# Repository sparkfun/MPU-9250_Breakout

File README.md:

9 Degrees of Freedom - MPU-9250 Breakout
========================================

[*9 Degrees of Freedom - MPU-9250 Breakout (SEN-13762)*](https://www.sparkfun.com/products/13762)

The MPU-9250 is an accelerometer, gyro, and magnetometer all in a single package with an I<sup>2</sup>C. [The datasheet can be found here.](https://cdn.sparkfun.com/assets/learn_tutorials/5/5/0/MPU9250REV1.0.pdf)

There are two SparkFun Arduino libraries available for this sensor:

* [SparkFun MPU-9250 Breakout Library](https://github.com/sparkfun/SparkFun_MPU-9250_Breakout_Arduino_Library) -- Simple Arduino library that supports all accelerometer, gyroscope, and magnetometer reads from the MPU-9250.
* [SparkFun MPU-9250 Digital Motion Processing (DMP) Arduino Library](https://github.com/sparkfun/SparkFun_MPU-9250-DMP_Arduino_Library) -- More advanced library that includes support for the MPU-9250's digital motion processing (DMP) library. This provides support for features like tap-detection, orientation-detection, step-counting (pedometer), and quaternion-calculation. Only tested on ARM-based Arduino boards ([SparkFun SAMD21 Mini Breakout](https://www.sparkfun.com/products/13664), [SparkFun 9DoF Razor - M0](https://www.sparkfun.com/products/14001)

Repository Contents
-------------------

* **/Firmware** &mdash; An Arduino library with an example that sends raw sensor data, quaternions, and AHRS data out of the serial port
* **/Hardware** &mdash; All Eagle design files
* **/Production** &mdash; Test bed files and production panel files

Documentation
--------------
* **[Library](https://github.com/sparkfun/SparkFun_MPU-9250-DMP_Arduino_Library)** - Arduino library for the MPU-9250 Breakout.
* **[Hookup Guide](https://learn.sparkfun.com/tutorials/mpu-9250-hookup-guide)** - Basic hookup guide for the MPU-9250 Breakout.
* **[SparkFun Fritzing repo](https://github.com/sparkfun/Fritzing_Parts/blob/master/products/13762_sfe_imu_sensor_9250.fzpz)** - Fritzing diagrams for SparkFun products.

License Information
-------------------
The hardware is released under [Creative Commons Share-alike 4.0](http://creativecommons.org/licenses/by-sa/4.0/).  
The firmware is released under the [Beerware license](http://en.wikipedia.org/wiki/Beerware).

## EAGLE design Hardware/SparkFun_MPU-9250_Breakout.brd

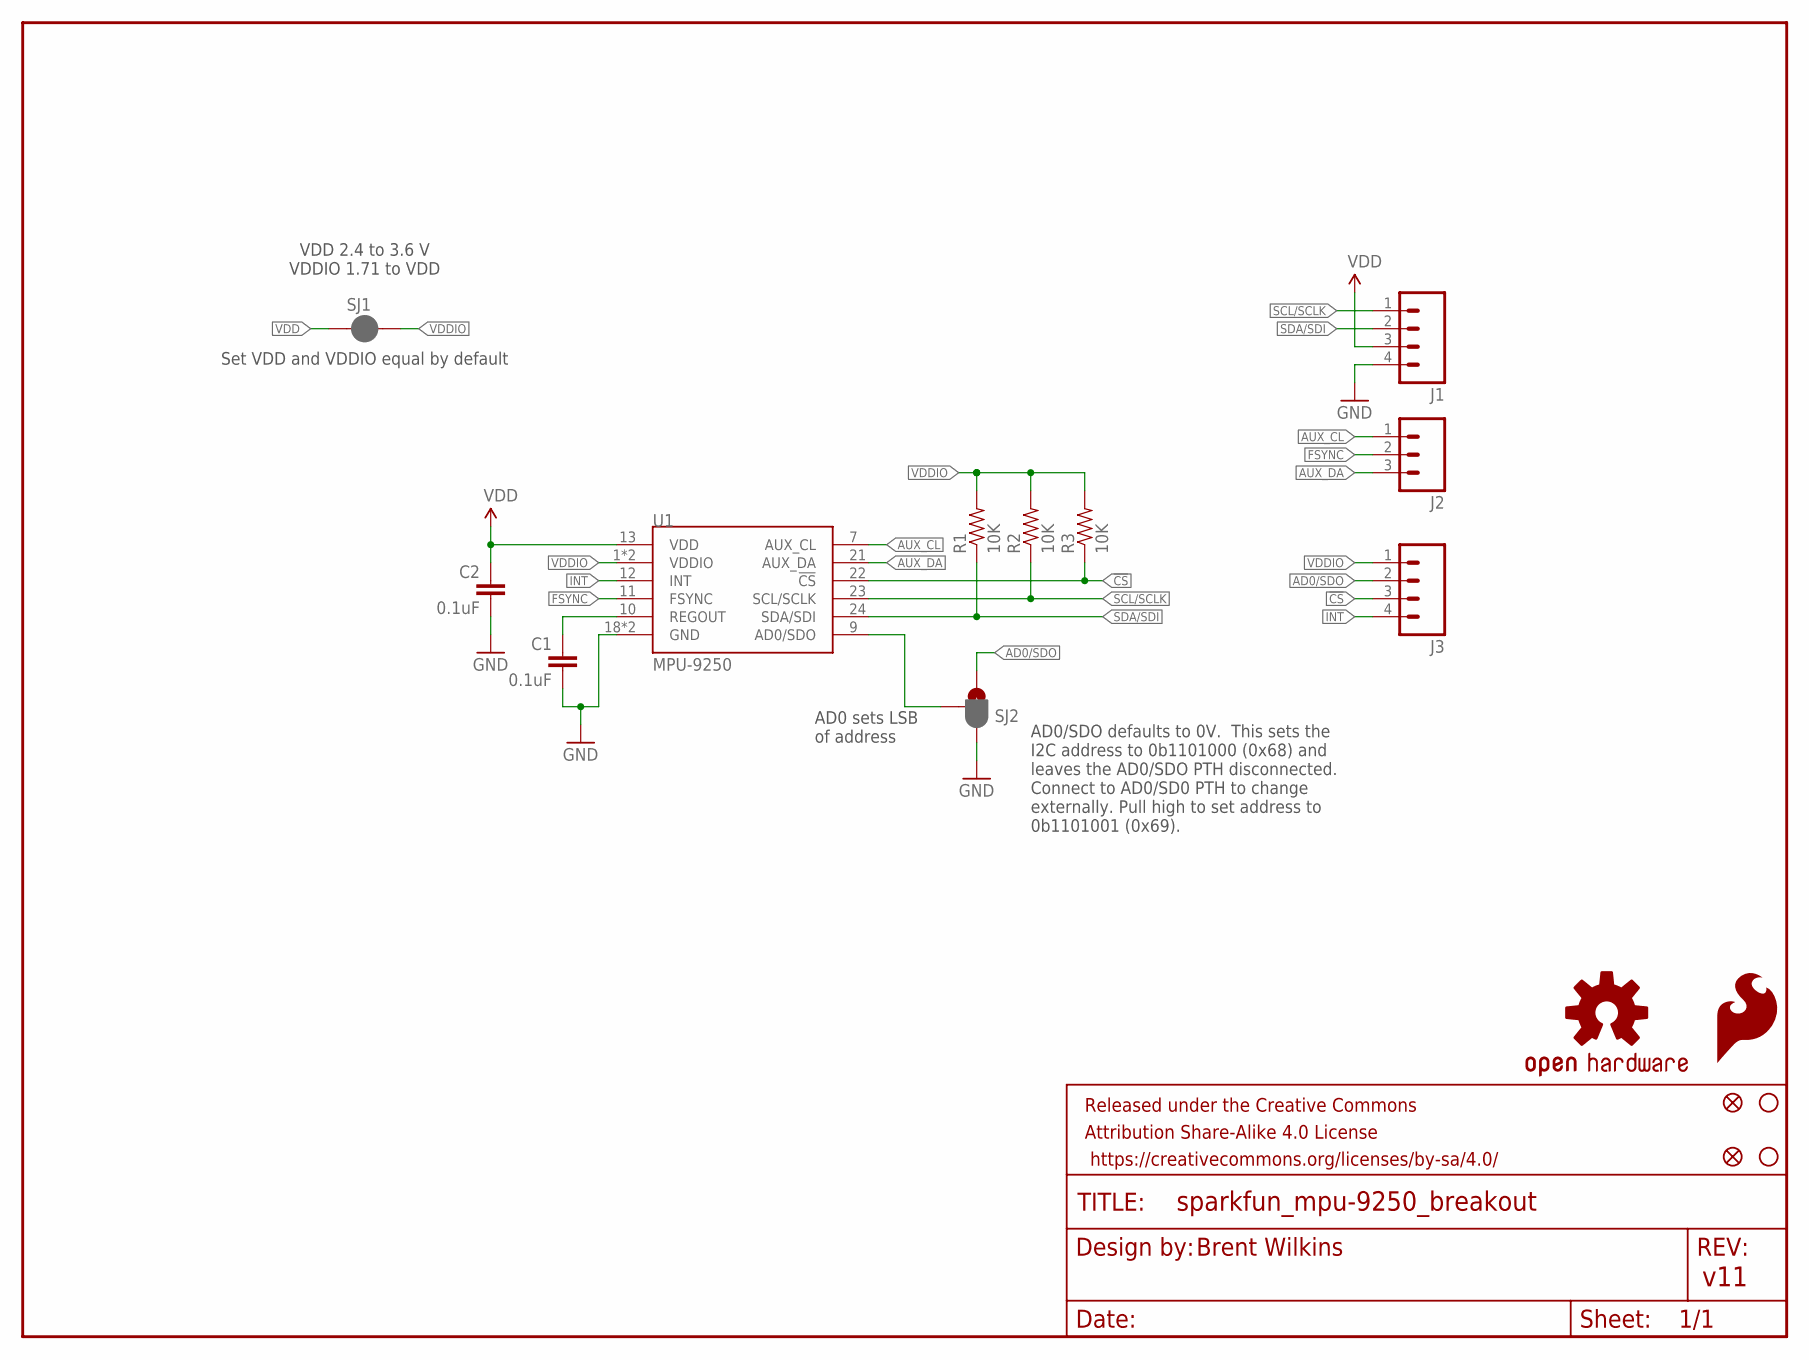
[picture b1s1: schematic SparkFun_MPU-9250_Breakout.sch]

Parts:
C1, C2: 0.1uF; 0603-CAP
FID1, FID2: FIDUCIAL1X2; FIDUCIAL-1X2
FRAME1: FRAME-LETTER; CREATIVE_COMMONS
J1, J3: M04PTH; 1X04
J2: M03PTH; 1X03
LOGO1: SFE_LOGO_FLAME.1_INCH; SFE_LOGO_FLAME_.1
LOGO2: OSHW-LOGOS; OSHW-LOGO-S
R1, R2, R3: 10K; 0603-RES
SJ1: JUMPER-PAD-2-NC_BY_PASTEFULL-BOX-SILK; PAD-JUMPER-2-NC_BY_PASTE_YES_SILK_FULL_BOX
SJ2: JUMPER_PAD-3-1&2_NC_BY_PASTE; PAD-HUMPER-3-1&2_NC_BY_PASTE_YES_SILK_FULL_BOX
STANDOFF1, STANDOFF2: STAND-OFF
U1: MPU-9250; QFN24

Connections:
!CS: J3.3, R3.1, U1.22 (!CS)
AD0/SDO: J3.2, SJ2.3
ADSD_STUB: SJ2.2, U1.9 (AD0/SDO)
AUX_CL: J2.1, U1.7 (AUX_CL)
AUX_DA: J2.3, U1.21 (AUX_DA)
FSYNC: J2.2, U1.11 (FSYNC)
GND: C1.2, C2.2, J1.4, SJ2.1, U1.18 (GND), U1.20 (GND)
INT: J3.4, U1.12 (INT)
REGOUT: C1.1, U1.10 (REGOUT)
SCL/SCLK: J1.1, R2.1, U1.23 (SCL/SCLK)
SDA/SDI: J1.2, R1.1, U1.24 (SDA/SDI)
VDD: C2.1, J1.3, SJ1.1, U1.13 (VDD)
VDDIO: J3.1, R1.2, R2.2, R3.2, SJ1.2, U1.1 (VDDIO), U1.8 (VDDIO)

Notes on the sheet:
AD0/SDO defaults to 0V. This sets the I2C address to 0b1101000 (0x68) and leaves the AD0/SDO PTH disconnected. Connect to AD0/SD0 PTH to change externally. Pull high to set address to 0b1101001 (0x69).
AD0 sets LSB of address
Set VDD and VDDIO equal by default
VDD 2.4 to 3.6 V VDDIO 1.71 to VDD

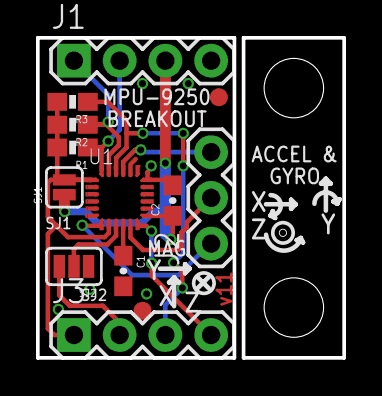
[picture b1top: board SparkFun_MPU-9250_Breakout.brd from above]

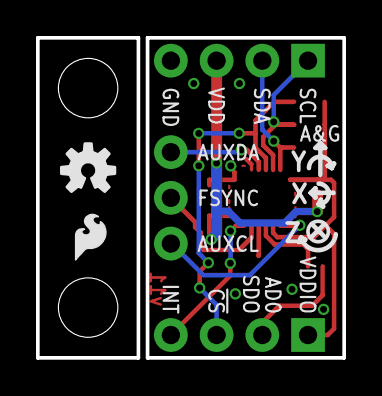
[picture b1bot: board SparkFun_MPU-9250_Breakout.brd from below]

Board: 2 copper layers, 17.0 x 17.8 mm, 18 parts (2 on the bottom side), 13 nets.

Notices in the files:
parts and their libraries:
SparkFun-Aesthetics: Licensing: Creative Commons ShareAlike 4.0 International - https://creativecommons.org/licenses/by-sa/4.0
SparkFun-Aesthetics: Released under the Creative Commons Attribution Share-Alike 4.0 License
SparkFun-Aesthetics: https://creativecommons.org/licenses/by-sa/4.0
